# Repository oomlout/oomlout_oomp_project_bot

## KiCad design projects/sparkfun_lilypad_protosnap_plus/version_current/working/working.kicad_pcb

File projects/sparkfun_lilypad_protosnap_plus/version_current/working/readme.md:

# OOMP Project  
## LilyPad_ProtoSnap_Plus  by sparkfun  
  
oomp key: oomp_projects_flat_sparkfun_lilypad_protosnap_plus  
(snippet of original readme)  
  
SparkFun LilyPad ProtoSnap Plus  
========================================  
  
<table class="table table-hover table-striped table-bordered">  
  <tr>  
   <td><a href="https://www.sparkfun.com/products/14346"><div align="center"></div></a></center></td>  
   <td><a href="https://www.sparkfun.com/products/12922"><div align="center"></div></a></td>  
  </tr>  
  <tr>  
    <td><div align="center">LilyPad ProtoSnap Plus [<a href="https://www.sparkfun.com/products/14346">DEV-14346</a> ]</div></td>  
    <td><div align="center">LilyPad ProtoSnap Plus Kit [<a href="https://www.sparkfun.com/products/12922">DEV-12922</a>]</div></td>  
  </tr>  
</table>  
  
Snappable prototyping board with 32u4, light sensor, buzzer, button, and leds.   
  
To use the ProtoSnap Plus with Arduino, install the [SparkFun Arduino_Boards](https://github.com/sparkfun/Arduino_Boards) package for avr version 1.1.7 or later.  
  
Base examples for this board are included in the package.  Select "LilyPad USB Plus" as a board type, then see examples for that board.  
  
For extra information on Linux use, see [/Documentation/LinuxInstallation.md](https://github.com/sparkfun/LilyPad_ProtoSnap_Plus/tree/master/Documentation/LinuxInstallation.md).  
  
Repository Contents  
-------------------  
  
* **/Documentation** - pin mapping and design informatio  
  full source readme at [readme_src.md](readme_src.md)  
  
source repo at: [https://github.com/sparkfun/LilyPad_ProtoSnap_Plus](https://github.com/sparkfun/LilyPad_ProtoSnap_Plus)  
## Board  

## Schematic  

[schematic pdf](working_schematic.pdf)  
## Images

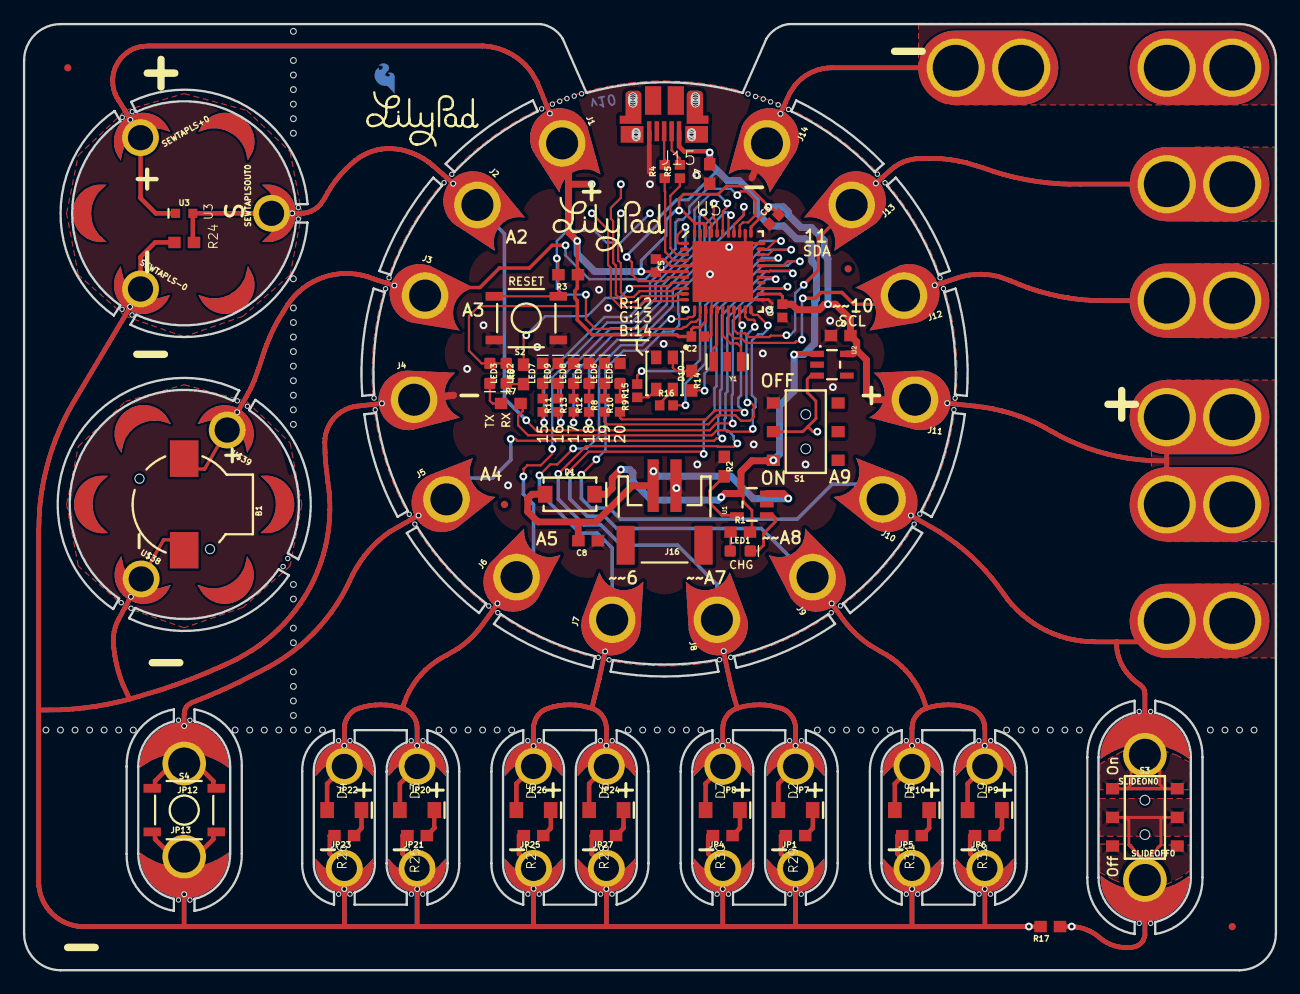
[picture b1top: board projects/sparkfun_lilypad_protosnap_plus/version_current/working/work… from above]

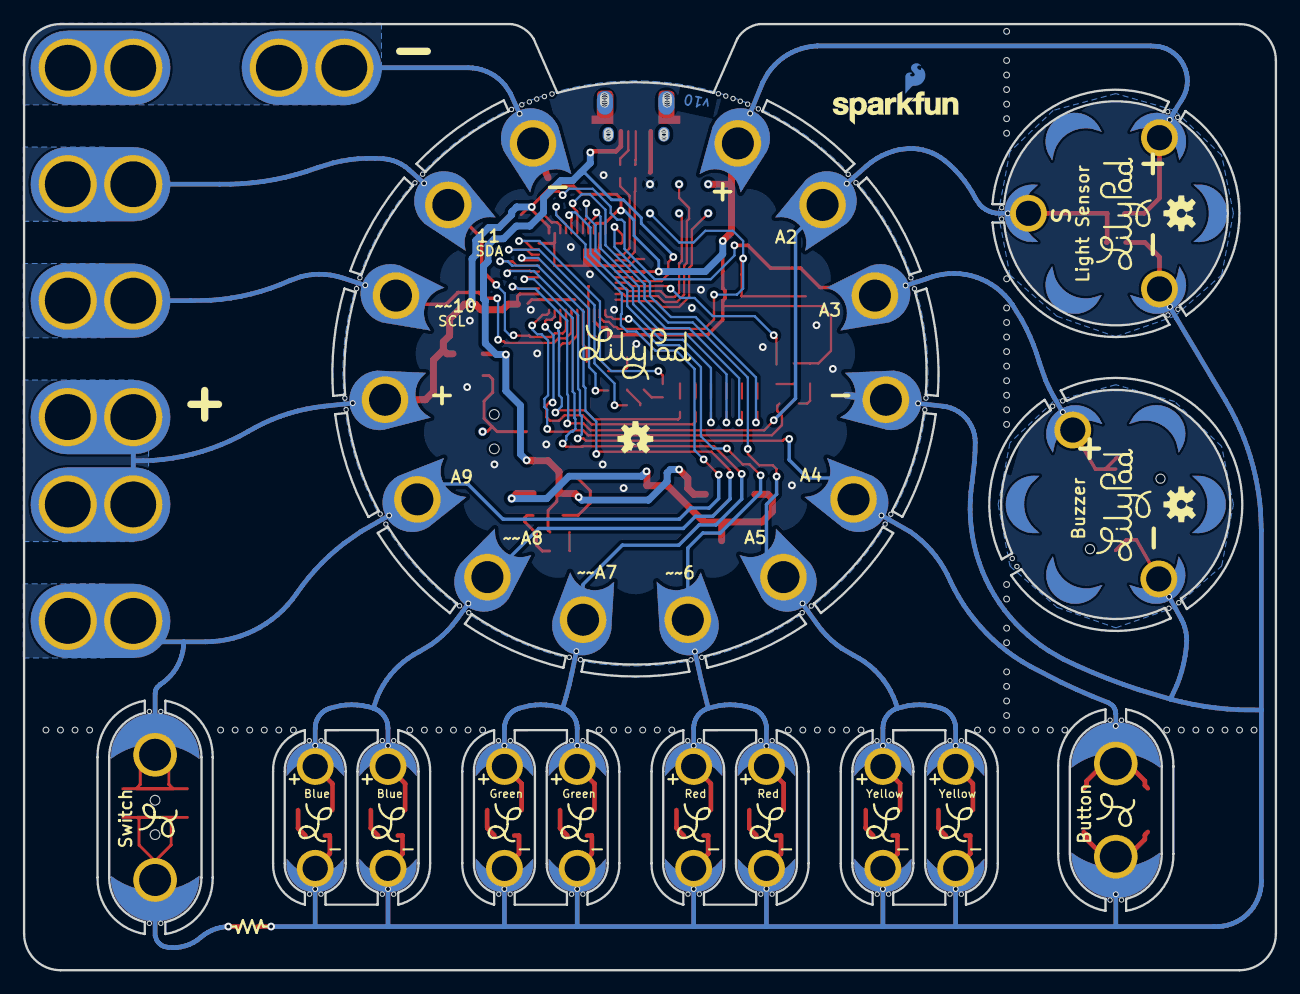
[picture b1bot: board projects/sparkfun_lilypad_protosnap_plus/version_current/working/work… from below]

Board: 2 copper layers, 109.2 x 82.6 mm, 352 parts (26 on the bottom side), 59 nets.

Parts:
@HOLE0, @HOLE1, @HOLE2, @HOLE3, @HOLE4, @HOLE5, @HOLE6, @HOLE7, @HOLE8, @HOLE9, @HOLE10, @HOLE11, @HOLE12, @HOLE13, @HOLE14, @HOLE15, @HOLE16, @HOLE17, @HOLE18, @HOLE19, @HOLE20, @HOLE21, @HOLE22, @HOLE23, @HOLE24, @HOLE25, @HOLE26, @HOLE27, @HOLE28, @HOLE29, @HOLE30, @HOLE31, @HOLE32, @HOLE33, @HOLE34, @HOLE35, @HOLE36, @HOLE37, @HOLE38, @HOLE39, @HOLE40, @HOLE41, @HOLE42, @HOLE43, @HOLE44, @HOLE45, @HOLE46, @HOLE47, @HOLE48, @HOLE49, @HOLE50, @HOLE51, @HOLE52, @HOLE53, @HOLE54, @HOLE55, @HOLE56, @HOLE57, @HOLE58, @HOLE59, @HOLE60, @HOLE61, @HOLE62, @HOLE63, @HOLE64, @HOLE65, @HOLE66, @HOLE67, @HOLE68, @HOLE69, @HOLE70, @HOLE71, @HOLE72, @HOLE73, @HOLE74, @HOLE75, @HOLE76, @HOLE77, @HOLE78, @HOLE79, @HOLE80, @HOLE81, @HOLE82, @HOLE83, @HOLE84, @HOLE85, @HOLE86, @HOLE87, @HOLE88, @HOLE89, @HOLE90, @HOLE91, @HOLE92, @HOLE93, @HOLE94, @HOLE95, @HOLE96, @HOLE97, @HOLE98, @HOLE99, @HOLE100, @HOLE101, @HOLE102, @HOLE103, @HOLE104, @HOLE105, @HOLE106, @HOLE107, @HOLE108, @HOLE109, @HOLE110, @HOLE111, @HOLE112, @HOLE113, @HOLE114, @HOLE115, @HOLE116, @HOLE117, @HOLE118, @HOLE119, @HOLE120, @HOLE121, @HOLE122, @HOLE123, @HOLE124, @HOLE125, @HOLE126, @HOLE127, @HOLE128, @HOLE129, @HOLE130, @HOLE131, @HOLE132, @HOLE133, @HOLE134, @HOLE135, @HOLE136, @HOLE137, @HOLE138, @HOLE139, @HOLE140, @HOLE141, @HOLE142, @HOLE143, @HOLE144, @HOLE145, @HOLE146, @HOLE147, @HOLE148, @HOLE149, @HOLE150, @HOLE151, @HOLE152, @HOLE153, @HOLE154: (no value)
B1: Buzzer; BUZZER-CCV
C2, C3, C4: 0.1uF; 0402
C5: 1.0uF; 0402
C6, C7, C8: 4.7uF; 0603
D1: 3A/40V/500mV; SMA-DIODE
D2, D7: GREEN; LED-1206
D3, D4: Yellow; LED-1206
D5, D6: RED; LED-1206
D8, D9: BLUE; LED-1206
D10: XZM2CRKM2DGFBB45SCCB; PLCC4SMDLED
FRAME1: FRAME-LETTER; CREATIVE_COMMONS
FRAME2: FRAME-LETTERNO_PACKAGE; DUMMY
J1, J2, J3, J4, J5, J6, J7, J8, J9, J10, J11, J12, J13, J14: SEWTAP_LONG-2SIDE; PETAL-LONG-1-2SIDE
J15: AMP FCI 10103594-0001LF; USB-MICROB-PTH
J16: JST-2-SMD
JP1, JP4, JP5, JP6, JP7, JP8, JP9, JP10, JP20, JP21, JP22, JP23, JP24, JP25, JP26, JP27: SEWTAP_SMALL-2SIDE; PETAL-SMALL-2SIDE
JP2, JP3, JP11, JP14: FIDUCIALUFIDUCIAL; MICRO-FIDUCIAL
JP12, JP13: SEWTAP_MEDIUM-2SIDE; PETAL-MEDIUM-2SIDE
L001, L002, L003, L004: LOGO-L
LED1: RED; LED-0603
LED2: Yellow; LED-0603
LED3: GREEN; LED-0603
LED4, LED5, LED6, LED7, LED8, LED9: WHITE; LED-0603
LOGO1: SFE_LOGO_NAME.1_INCH; SFE_LOGO_NAME_.1
LOGO2: SFE_LOGO_FLAME.1EXP; SFE_LOGO_FLAME_COPPER_EXPOSED_.1
LOGO4, LOGO5, LOGO6: OSHW-LOGOS; OSHW-LOGO-S
R1, R7, R14: 330; 0603
R2, R3, R24: 10k; 0603
R4, R5, R15, R16: 22; 0402
R6: 2.2k; 0603
R8, R9, R10, R11, R12, R13: 470; 0402
R17: 1k; 0603
R25, R26, R29, R30: 100; 0603
R27, R28, R31, R32: 150; 0603
S1, S3: SWITCH_DPDT_SMD_AYZ0202
S2: !RESET; TACTILE_SWITCH_SMD_5.2MM
S4: MOMENTARY-SWITCH-SPST-SMD-5.2-REDUNDANT; TACTILE_SWITCH_SMD_5.2MM
SEWTAPLS+0: PLUS; PETAL-SMALL-2SIDE
SEWTAPLS-0: MINUS; PETAL-SMALL-2SIDE
SEWTAPLSOUT0: OUT; PETAL-SMALL-2SIDE
SLIDEOFF0: SEWTAP_MEDIUM-2SIDE; PETAL-MEDIUM-2SIDE
SLIDEON0: SEWTAP_MEDIUM-2SIDE; PETAL-MEDIUM-2SIDE
ST1, ST2, ST3: SEWTAP-NOHOLE_SM_NH; PETAL-SMALL-NOHOLE
TP1, TP2, TP3, TP4, TP5, TP6, TP7, TP8: TEST-POINT3; PAD.03X.03
U1: MCP73831; SOT23-5
U2: 3.3V; SOT23-5
U3: ALS-PT19
U5: 32U4; QFN-44-PAD_1_1-LESS_PASTE
U$1, U$5, U$6, U$13, U$43: LILYLOGO_SHORT; LILYPAD-WEARABLES_LOGO-LILYPAD
U$3, U$9, U$11, U$15, U$17, U$19, U$21, U$23, U$25, U$27, U$29, U$31, U$33, U$34: PETAL_PAD_OFF
U$7, U$8, U$10, U$12, U$16, U$18, U$20, U$22, U$24, U$26, U$28, U$30, U$32: PETAL_SPACE_OFF
U$35, U$36, U$37, U$40: SEWTAP-NOHOLE_SM_NH; PETAL-SMALL-NOHOLE
U$38, U$39: SEWTAP_SMALL-2SIDE; PETAL-SMALL-2SIDE
U$41, U$42, U$51/SDA0, U$52/SCL0, U$52/SCL1, U$53, U$54: GATOR_HOLE_PAIR; GATOR_HOLES
U$44: SPECIAL_INSTRUCTIONS-ORDERING; ORDERING_INSTRUCTIONS
U$45, U$46, U$48, U$49, U$50: LOGO-L
U$51, U$52, U$55, U$56, U$57, U$58, U$59, U$60, U$61, U$62, U$63, U$64, U$65, U$66, U$67, U$68, U$70, U$71: ROUTE_TICKS
U$73: LILYLOGO_ABR; LILYPAD-WEARABLES_LOGO-L
Y1: 8MHz; RESONATOR-SMD

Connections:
3.3V: C2.2, C3.2, C4.2, C5.2, C6.2, J1.1, J11.1, LED2.A, LED3.A, R3.1, SEWTAPLS+0.1, TP6.P$1, U2.5, U3.C, U5.6, U5.14, U5.24, U5.34, U5.42, U5.44, U$41.P$1, U$41.P$2, U$42.P$1, U$42.P$2
BG_LED0: R8.2, U5.38
BG_LED1: R9.2, U5.20
BG_LED2: R10.2, U5.21
BG_LED3: R11.2, U5.1
BG_LED4: R12.2, U5.40
BG_LED5: R13.2, U5.41
D2: J2.1, R24.2, SEWTAPLSOUT0.1, U3.E, U5.25
D3: B1.+, J3.1, U5.36, U$39.1
D4: J5.1, JP12.1, S4.1, S4.2, U5.28
D5: D3.A, D4.A, J6.1, JP20.1, JP22.1, U5.39
D6: D5.A, D6.A, J7.1, JP24.1, JP26.1, U5.12
D7: D2.A, D7.A, J8.1, JP7.1, JP8.1, U5.27
D8: D8.A, D9.A, J9.1, JP9.1, JP10.1, U5.29
D9: J10.1, S3.1, S3.4, SLIDEON0.1, U5.37, U$52/SCL1.P$1, U$52/SCL1.P$2
D10: J12.1, U5.18, U$52/SCL0.P$1, U$52/SCL0.P$2
D11: J13.1, U5.19, U$51/SDA0.P$1, U$51/SDA0.P$2
D+: R4.1, U5.4
D-: R5.1, U5.3
GND: B1.-, C2.1, C3.1, C4.1, C5.1, C6.1, C7.1, C8.1, D10.4, J4.1, J14.1, J15.GND, J16.1, JP1.1, JP4.1, JP5.1, JP6.1, JP13.1, JP21.1, JP23.1, JP25.1, JP27.1, LED4.C, LED5.C, LED6.C, LED7.C, LED8.C, LED9.C, R2.1, R17.2, R24.1, R25.1, R26.1, R27.1, R28.1, R29.1, R30.1, R31.1, R32.1, S1.3, S2.1, S2.2, S4.3, S4.4, SEWTAPLS-0.1, TP5.P$1, U1.2, U2.2, U5.5, U5.15, U5.23, U5.33, U5.35, U5.43, U$38.1, U$53.P$1, U$53.P$2, U$54.P$1, U$54.P$2, Y1.2
MISO: TP1.P$1, U5.11
MOSI: TP2.P$1, U5.10
unnamed: LED2.C, R6.1
unnamed: S1.2, TP8.P$1, U2.3
unnamed: LED1.A, R1.1
unnamed: LED1.C, U1.1
unnamed: U5.17, Y1.1
unnamed: R2.2, U1.5
unnamed: U5.16, Y1.3
unnamed: D10.2, R16.1
unnamed: LED7.A, R11.1
unnamed: LED6.A, R10.1
unnamed: LED5.A, R9.1
unnamed: LED8.A, R12.1
unnamed: LED9.A, R13.1
unnamed: D10.3, R15.1
unnamed: D10.1, R14.1
unnamed: LED4.A, R8.1
unnamed: J15.D-, R5.2
unnamed: J15.D+, R4.2
unnamed: LED3.C, R7.1
unnamed: D3.C, R25.2
unnamed: D4.C, R26.2
unnamed: D5.C, R27.2
unnamed: D6.C, R28.2
unnamed: D2.C, R29.2
RESET: R3.2, S2.3, S2.4, TP4.P$1, U5.13
RGB_B: R15.2, U5.32
RGB_G: R16.2, U5.31
RGB_R: R14.2, U5.30
RX_LED: R6.2, U5.8
SCK: TP3.P$1, U5.9
SEWTAP+1: D7.C, R30.2
TX_LED: R7.2, U5.22
VCC_1: C7.2, D1.C, J15.VBUS, R1.2, S1.1, U1.4, U2.1, U5.7
V_BATT: C8.2, D1.A, J16.2, TP7.P$1, U1.3
X003: D8.C, R31.2
X004: D9.C, R32.2
X005: R17.1, S3.2, S3.5, SLIDEOFF0.1

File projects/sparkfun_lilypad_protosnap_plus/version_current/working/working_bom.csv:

"Id";"Designator";"Footprint";"Quantity";"Designation";"Supplier and ref";
1;"@HOLE147,@HOLE118,@HOLE117,@HOLE103,@HOLE99,@HOLE35,@HOLE28,@HOLE144,@HOLE55,@HOLE115,@HOLE102,@HOLE146,@HOLE45,@HOLE151,@HOLE29,@HOLE77,@HOLE61,@HOLE40,@HOLE1,@HOLE81,@HOLE137,@HOLE21,@HOLE2,@HOLE25,@HOLE47,@HOLE18,@HOLE149,@HOLE5,@HOLE93,@HOLE132,@HOLE44,@HOLE13,@HOLE59,@HOLE57,@HOLE133,@HOLE120,@HOLE134,@HOLE87,@HOLE136,@HOLE107,@HOLE73,@HOLE68,@HOLE121,@HOLE76,@HOLE70,@HOLE30,@HOLE52,@HOLE31,@HOLE19,@HOLE50,@HOLE69,@HOLE71,@HOLE20,@HOLE104,@HOLE91,@HOLE79,@HOLE105,@HOLE72,@HOLE111,@HOLE83,@HOLE123,@HOLE67,@HOLE56,@HOLE9,@HOLE153,@HOLE108,@HOLE80,@HOLE129,@HOLE48,@HOLE125,@HOLE89,@HOLE126,@HOLE98,@HOLE90,@HOLE36,@HOLE66,@HOLE63,@HOLE0,@HOLE7,@HOLE114,@HOLE143,@HOLE8,@HOLE97,@HOLE11,@HOLE142,@HOLE14,@HOLE152,@HOLE122,@HOLE74,@HOLE116,@HOLE46,@HOLE110,@HOLE131,@HOLE22,@HOLE27,@HOLE85,@HOLE51,@HOLE145,@HOLE32,@HOLE54,@HOLE4,@HOLE140,@HOLE113,@HOLE78,@HOLE10,@HOLE6,@HOLE39,@HOLE43,@HOLE135,@HOLE96,@HOLE15,@HOLE41,@HOLE17,@HOLE34,@HOLE84,@HOLE94,@HOLE100,@HOLE124,@HOLE86,@HOLE58,@HOLE75,@HOLE106,@HOLE128,@HOLE141,@HOLE92,@HOLE53,@HOLE130,@HOLE42,@HOLE33,@HOLE65,@HOLE64,@HOLE16,@HOLE38,@HOLE119,@HOLE95,@HOLE88,@HOLE24,@HOLE82,@HOLE101,@HOLE62,@HOLE109,@HOLE138,@HOLE49,@HOLE37,@HOLE3,@HOLE139,@HOLE112,@HOLE23,@HOLE150,@HOLE154,@HOLE127,@HOLE60,@HOLE148,@HOLE12,@HOLE26";"";155;"";;;
2;"U$52/SCL0,U$52/SCL1,U$51/SDA0,U$42,U$41,U$54,U$53";"GATOR_HOLES";7;"GATOR_HOLE_PAIR";;;
3;"LED4,LED6,LED8,LED9,LED5,LED7";"LED-0603";6;"WHITE";;;
4;"U$58,U$71,U$66,U$68,U$52,U$63,U$60,U$57,U$65,U$67,U$61,U$64,U$62,U$56,U$51,U$70,U$59,U$55";"ROUTE_TICKS";18;"";;;
5;"JP23,JP24,JP25,JP26,JP5,JP21,JP22,JP10,U$39,JP7,JP8,JP20,JP6,JP9,JP27,JP1,U$38,JP4";"PETAL-SMALL-2SIDE";18;"SEWTAP_SMALL-2SIDE";;;
6;"R16,R5,R4,R15";"0402";4;"22";;;
7;"D9,D8";"LED-1206";2;"BLUE";;;
8;"J2,J5,J1,J4,J6,J3,J7,J11,J9,J13,J8,J14,J10,J12";"PETAL-LONG-1-2SIDE";14;"SEWTAP_LONG-2SIDE";;;
9;"R11,R8,R9,R10,R13,R12";"0402";6;"470";;;
10;"U$32,U$28,U$20,U$24,U$16,U$7,U$18,U$8,U$30,U$26,U$22,U$10,U$12";"PETAL_SPACE_OFF";13;"";;;
11;"R24,R2,R3";"0603";3;"10k";;;
12;"Y1";"RESONATOR-SMD";1;"8MHz";;;
13;"S4";"TACTILE_SWITCH_SMD_5.2MM";1;"MOMENTARY-SWITCH-SPST-SMD-5.2-REDUNDANT";;;
14;"ST3,U$36,U$35,U$40,U$37,ST1,ST2";"PETAL-SMALL-NOHOLE";7;"SEWTAP-NOHOLE_SM_NH";;;
15;"R26,R25,R29,R30";"0603";4;"100";;;
16;"R6";"0603";1;"2.2k";;;
17;"U$27,U$31,U$21,U$25,U$11,U$15,U$3,U$33,U$19,U$9,U$29,U$23,U$34,U$17";"PETAL_PAD_OFF";14;"";;;
18;"C5";"0402";1;"1.0uF";;;
19;"S3,S1";"SWITCH_DPDT_SMD_AYZ0202";2;"";;;
20;"FRAME2";"DUMMY";1;"FRAME-LETTERNO_PACKAGE";;;
21;"C8,C7,C6";"0603";3;"4.7uF";;;
22;"J16";"JST-2-SMD";1;"";;;
23;"JP12,SLIDEOFF0,SLIDEON0,JP13";"PETAL-MEDIUM-2SIDE";4;"SEWTAP_MEDIUM-2SIDE";;;
24;"D10";"PLCC4SMDLED";1;"XZM2CRKM2DGFBB45SCCB";;;
25;"R32,R31,R27,R28";"0603";4;"150";;;
26;"S2";"TACTILE_SWITCH_SMD_5.2MM";1;"!RESET";;;
27;"LED1";"LED-0603";1;"RED";;;
28;"LED3";"LED-0603";1;"GREEN";;;
29;"R17";"0603";1;"1k";;;
30;"U$43,U$13,U$6,U$5,U$1";"LILYPAD-WEARABLES_LOGO-LILYPAD";5;"LILYLOGO_SHORT";;;
31;"D4,D3";"LED-1206";2;"Yellow";;;
32;"JP3,JP11,JP2,JP14";"MICRO-FIDUCIAL";4;"FIDUCIALUFIDUCIAL";;;
33;"U2";"SOT23-5";1;"3.3V";;;
34;"D6,D5";"LED-1206";2;"RED";;;
35;"U$44";"ORDERING_INSTRUCTIONS";1;"SPECIAL_INSTRUCTIONS-ORDERING";;;
36;"R7,R14,R1";"0603";3;"330";;;
37;"U3";"ALS-PT19";1;"ALS-PT19";;;
38;"C2,C3,C4";"0402";3;"0.1uF";;;
39;"LED2";"LED-0603";1;"Yellow";;;
40;"D2,D7";"LED-1206";2;"GREEN";;;
41;"U1";"SOT23-5";1;"MCP73831";;;
42;"U5";"QFN-44-PAD_1_1-LESS_PASTE";1;"32U4";;;
43;"D1";"SMA-DIODE";1;"3A/40V/500mV";;;
44;"FRAME1";"CREATIVE_COMMONS";1;"FRAME-LETTER";;;
45;"J15";"USB-MICROB-PTH";1;"AMP FCI 10103594-0001LF";;;
46;"B1";"BUZZER-CCV";1;"Buzzer";;;
47;"SEWTAPLSOUT0";"PETAL-SMALL-2SIDE";1;"OUT";;;
48;"SEWTAPLS-0";"PETAL-SMALL-2SIDE";1;"MINUS";;;
49;"SEWTAPLS+0";"PETAL-SMALL-2SIDE";1;"PLUS";;;
50;"U$49,L001,U$45,U$48,L004,L002,U$46,L003,U$50";"LOGO-L";9;"";;;
51;"TP6,TP2,TP7,TP1,TP8,TP3,TP4,TP5";"PAD.03X.03";8;"TEST-POINT3";;;
52;"U$73";"LILYPAD-WEARABLES_LOGO-L";1;"LILYLOGO_ABR";;;
53;"LOGO6,LOGO5,LOGO4";"OSHW-LOGO-S";3;"OSHW-LOGOS";;;
54;"LOGO1";"SFE_LOGO_NAME_.1";1;"SFE_LOGO_NAME.1_INCH";;;
55;"LOGO2";"SFE_LOGO_FLAME_COPPER_EXPOSED_.1";1;"SFE_LOGO_FLAME.1EXP";;;

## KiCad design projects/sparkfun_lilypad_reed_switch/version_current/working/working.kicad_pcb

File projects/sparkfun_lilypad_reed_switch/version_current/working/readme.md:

# OOMP Project  
## LilyPad_Reed_Switch  by sparkfun  
  
oomp key: oomp_projects_flat_sparkfun_lilypad_reed_switch  
(snippet of original readme)  
  
SparkFun LilyPad Reed Switch  
========================================  

[*LilyPad Reed Switch (DEV-13343)*](https://www.sparkfun.com/products/13343)  
  
A magnetically-activated switch designed for easy use in e-textiles projects.  
  
Repository Contents  
-------------------  
  
* **/Hardware** - Eagle design files (.brd, .sch)  
* **/Production** - Production panel files (.brd)  
  
Documentation  
--------------  
  
* **[Hookup Guide](https://learn.sparkfun.com/tutorials/lilypad-reed-switch-hookup-guide?_ga=1.257312139.1628578815.1436805952)** - Basic hookup guide for the LilyPad Reed Switch.  
* **[SparkFun Fritzing repo](https://github.com/sparkfun/Fritzing_Parts)** - Fritzing diagrams for SparkFun products.  
* **[SparkFun 3D Model repo](https://github.com/sparkfun/3D_Models)** - 3D models of SparkFun products.   

License Information  
-------------------  
  
This product is _**open source**_!   
  
Please review the LICENSE.md file for license information.   
  
If you have any questions or concerns on licensing, please contact techsupport@sparkfun.com.  
  
Distributed as-is; no warranty is given.  
  
<3 <3 <3 Your friends at SparkFun.  
  
_Created in collaboration with Dr. Leah Buechley_  
  
  full source readme at [readme_src.md](readme_src.md)  
  
source repo at: [https://github.com/sparkfun/LilyPad_Reed_Switch](https://github.com/sparkfun/LilyPad_Reed_Switch)  
## Board  

## Schematic  

[schematic pdf](working_schematic.pdf)  
## Images

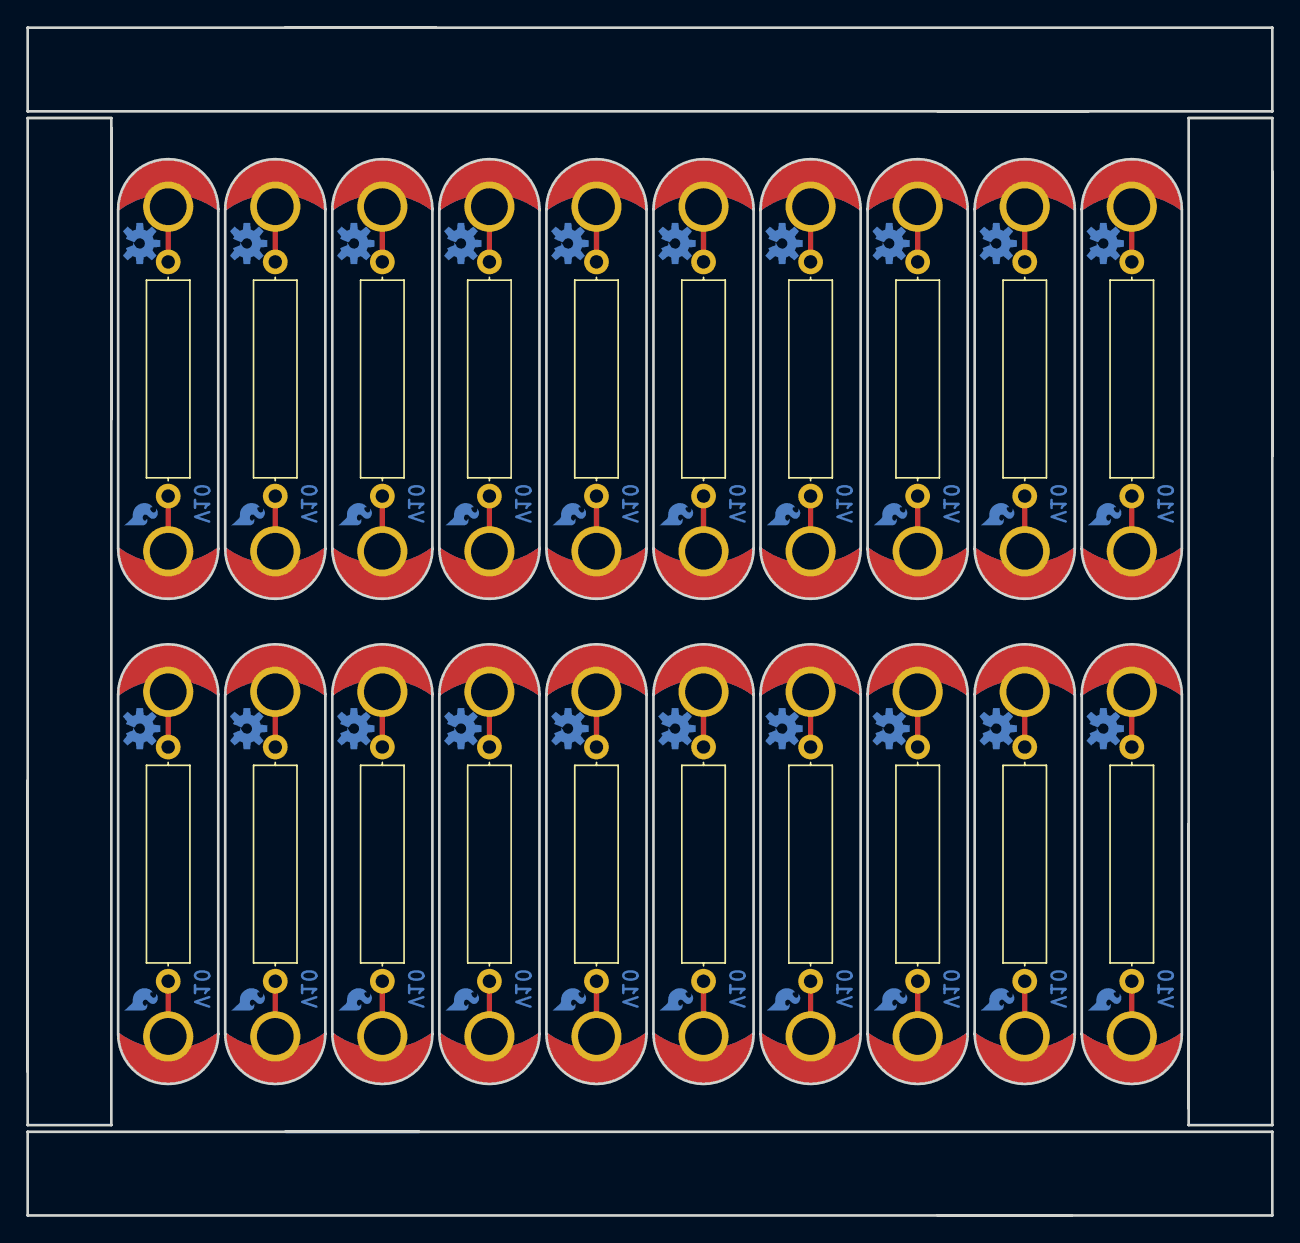
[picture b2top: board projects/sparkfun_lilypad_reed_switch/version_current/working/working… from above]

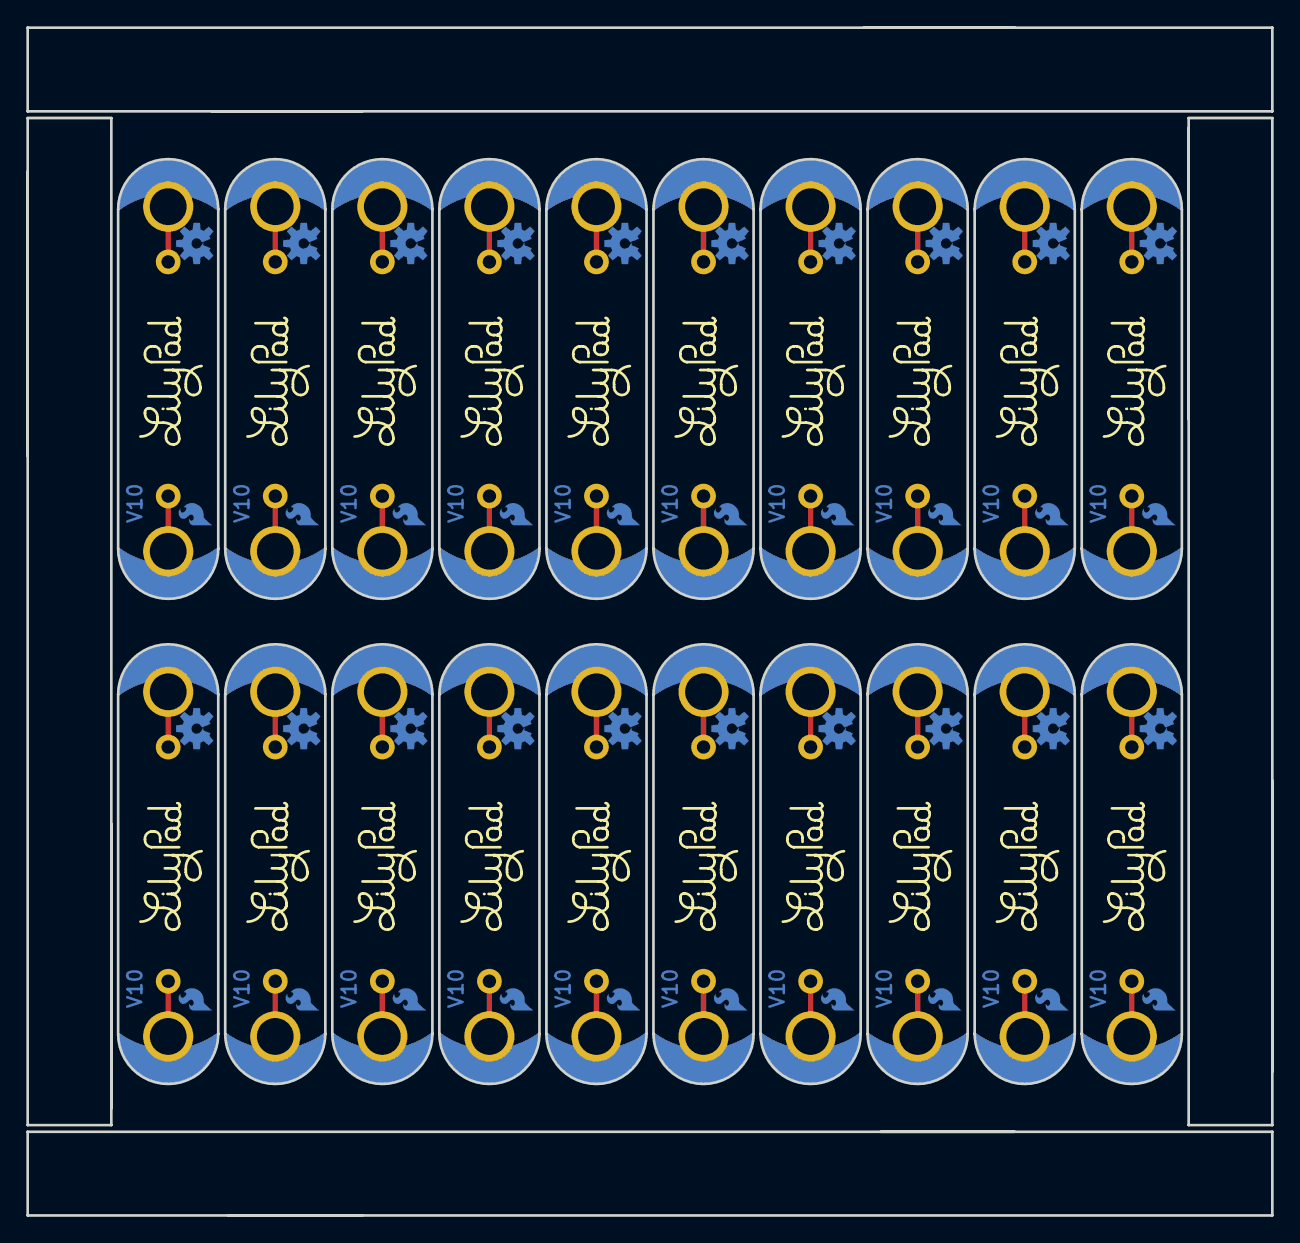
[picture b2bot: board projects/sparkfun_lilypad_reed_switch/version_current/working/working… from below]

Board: 4 copper layers, 94.5 x 90.2 mm, 120 parts (60 on the bottom side), 40 nets.

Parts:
LOGO1, LOGO3, LOGO5, LOGO7, LOGO9, LOGO11, LOGO13, LOGO15, LOGO17, LOGO19, LOGO21, LOGO23, LOGO25, LOGO27, LOGO29, LOGO31, LOGO33, LOGO35, LOGO37, LOGO39: OSHW-LOGOS-COPPER; OSHW-LOGO-S_COPPER
LOGO2, LOGO4, LOGO6, LOGO8, LOGO10, LOGO12, LOGO14, LOGO16, LOGO18, LOGO20, LOGO22, LOGO24, LOGO26, LOGO28, LOGO30, LOGO32, LOGO34, LOGO36, LOGO38, LOGO40: SFE_LOGO_FLAME.1COP; SFE_LOGO_FLAME_COPPER_.1
S1, S2, S3, S4, S5, S6, S7, S8, S9, S10, S11, S12, S13, S14, S15, S16, S17, S18, S19, S20: REED; REED_SWITCH_PLASTIC
SLIDEOFF0, SLIDEOFF1, SLIDEOFF2, SLIDEOFF3, SLIDEOFF4, SLIDEOFF5, SLIDEOFF6, SLIDEOFF7, SLIDEOFF8, SLIDEOFF9, SLIDEOFF10, SLIDEOFF11, SLIDEOFF12, SLIDEOFF13, SLIDEOFF14, SLIDEOFF15, SLIDEOFF16, SLIDEOFF17, SLIDEOFF18, SLIDEOFF19: SEWTAP8; PETAL-MEDIUM-2SIDE
SLIDEON0, SLIDEON1, SLIDEON2, SLIDEON3, SLIDEON4, SLIDEON5, SLIDEON6, SLIDEON7, SLIDEON8, SLIDEON9, SLIDEON10, SLIDEON11, SLIDEON12, SLIDEON13, SLIDEON14, SLIDEON15, SLIDEON16, SLIDEON17, SLIDEON18, SLIDEON19: SEWTAP8; PETAL-MEDIUM-2SIDE
U$1, U$2, U$3, U$4, U$5, U$6, U$7, U$8, U$9, U$10, U$11, U$12, U$13, U$14, U$15, U$16, U$17, U$18, U$19, U$20: LOGO-LPLP; LOGO-LILYPAD

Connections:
unnamed: S1.P$2, SLIDEOFF0.1
unnamed: S1.P$1, SLIDEON0.1
unnamed: S2.P$2, SLIDEOFF1.1
unnamed: S2.P$1, SLIDEON1.1
unnamed: S3.P$2, SLIDEOFF2.1
unnamed: S3.P$1, SLIDEON2.1
unnamed: S4.P$2, SLIDEOFF3.1
unnamed: S4.P$1, SLIDEON3.1
unnamed: S5.P$2, SLIDEOFF4.1
unnamed: S5.P$1, SLIDEON4.1
unnamed: S6.P$2, SLIDEOFF5.1
unnamed: S6.P$1, SLIDEON5.1
unnamed: S7.P$2, SLIDEOFF6.1
unnamed: S7.P$1, SLIDEON6.1
unnamed: S8.P$2, SLIDEOFF7.1
unnamed: S8.P$1, SLIDEON7.1
unnamed: S9.P$2, SLIDEOFF8.1
unnamed: S9.P$1, SLIDEON8.1
unnamed: S10.P$2, SLIDEOFF9.1
unnamed: S10.P$1, SLIDEON9.1
unnamed: S11.P$2, SLIDEOFF10.1
unnamed: S11.P$1, SLIDEON10.1
unnamed: S12.P$2, SLIDEOFF11.1
unnamed: S12.P$1, SLIDEON11.1
unnamed: S13.P$2, SLIDEOFF12.1
unnamed: S13.P$1, SLIDEON12.1
unnamed: S14.P$2, SLIDEOFF13.1
unnamed: S14.P$1, SLIDEON13.1
unnamed: S15.P$2, SLIDEOFF14.1
unnamed: S15.P$1, SLIDEON14.1
unnamed: S16.P$2, SLIDEOFF15.1
unnamed: S16.P$1, SLIDEON15.1
unnamed: S17.P$2, SLIDEOFF16.1
unnamed: S17.P$1, SLIDEON16.1
unnamed: S18.P$2, SLIDEOFF17.1
unnamed: S18.P$1, SLIDEON17.1
unnamed: S19.P$2, SLIDEOFF18.1
unnamed: S19.P$1, SLIDEON18.1
unnamed: S20.P$2, SLIDEOFF19.1
unnamed: S20.P$1, SLIDEON19.1

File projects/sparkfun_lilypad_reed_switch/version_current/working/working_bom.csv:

Row,Description,Part,References,Value,Footprint,Quantity Per PCB,Status,Datasheet
1,,FRAME-LETTER,FRAME1,FRAME-LETTER,CREATIVE_COMMONS,1, ,
2,,OSHW-LOGOS-COPPER,LOGO1,OSHW-LOGOS-COPPER,OSHW-LOGO-S_COPPER,1, ,
3,,SFE_LOGO_FLAME.1COP,LOGO2,SFE_LOGO_FLAME.1COP,SFE_LOGO_FLAME_COPPER_.1,1, ,
4,,SWITCH-MOMENTARY-2PTH_REED2,S1,SWITCH-MOMENTARY-2PTH_REED2,REED_SWITCH_PLASTIC,1, ,
5,,SEWTAP8,SLIDEOFF0 SLIDEON0,SEWTAP8,PETAL-MEDIUM-2SIDE,2, ,
6,,LOGO-LPLP,U$1,LOGO-LPLP,LOGO-LILYPAD,1, ,





Project info:
Schematic:,working
Variant:,default
Revision:,
Date:,2023-08-06_12-56-04
KiCad Version:,7.0.6-7.0.6~ubuntu22.04.1
Statistics:
Component Groups:,6
Component Count:,7 (0 SMD/ 0 THT)
Fitted Components:,7 (0 SMD/ 0 THT)
Number of PCBs:,1
Total Components:,7

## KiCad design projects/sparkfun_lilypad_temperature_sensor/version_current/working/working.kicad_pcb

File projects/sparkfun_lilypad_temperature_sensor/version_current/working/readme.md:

# OOMP Project  
## LilyPad_Temperature_Sensor  by sparkfun  
  
oomp key: oomp_projects_flat_sparkfun_lilypad_temperature_sensor  
(snippet of original readme)  
  
LilyPad Temperature Sensor  
========================================  

[*LilyPad Temperature Sensor (DEV-08777)*](https://www.sparkfun.com/products/8777)  
  
Detecting temperature changes has never been easier.   
The MCP9700 is a small thermistor type temperature sensor.   
This sensor will output 0.5V at 0 degrees C, 0.75V at 25 C, and 10mV per degree C. Doing an analog to digital conversion on the signal line will allow you to establish the local ambient temperature.   
Detect physical touch based on body heat and ambient conditions with this small sensor.  
  
Repository Contents  
-------------------  
* **/Firmware** - Arduino Example code   
* **/Hardware** - Eagle design files (.brd, .sch)  
* **/Production** - Production panel files (.brd)  
  
Documentation  
--------------  
* **[Hookup Guide](https://learn.sparkfun.com/tutorials/lilypad-temperature-sensor-hookup-guide)** - Basic Hookup Guide for the LilyPad temperature sensor.  
* **[SparkFun Fritzing repo](https://github.com/sparkfun/Fritzing_Parts)** - Fritzing diagrams for SparkFun products.  
* **[SparkFun 3D Model repo](https://github.com/sparkfun/3D_Models)** - 3D models of SparkFun products.   
  
License Information  
-------------------  
This product is _**open source**_!   
  
The **hardware** is released under [Creative Commons ShareAlike 4.0 International](https://creativecommons.org/licenses/by-sa/4.0/).  
  
Please use, reuse, and modify these files as you se  
  full source readme at [readme_src.md](readme_src.md)  
  
source repo at: [https://github.com/sparkfun/LilyPad_Temperature_Sensor](https://github.com/sparkfun/LilyPad_Temperature_Sensor)  
## Board  

## Schematic  

[schematic pdf](working_schematic.pdf)  
## Images

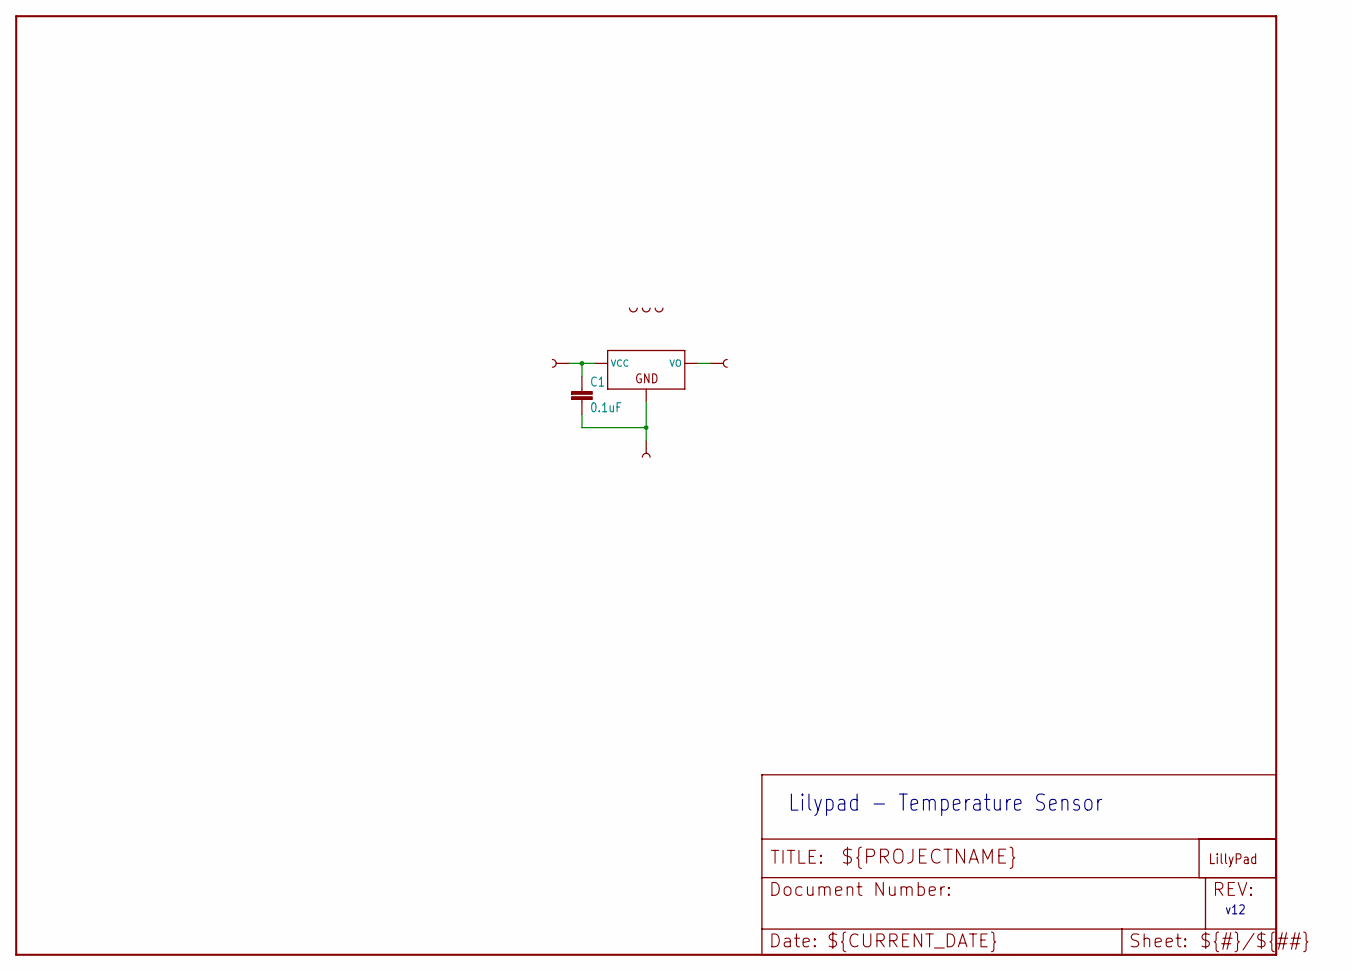
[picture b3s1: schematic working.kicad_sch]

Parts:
C1: 0.1uF; 0603-CAP
TEMP1, TEMP2, TEMP3: SEWTAP-NOHOLE2; PETAL-NOHOLE-2SIDE
TEMP+0: SEWTAP6; PETAL-SMALL-2SIDE
TEMP-0: SEWTAP6; PETAL-SMALL-2SIDE
TEMPS0: SEWTAP6; PETAL-SMALL-2SIDE
U1: MCP9700SMD; SOT23-3
U$2: LOGO-LPLP; LOGO-LILYPAD

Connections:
GND: C1.2, TEMP-0.1, U1.3 (GND)
VCC: C1.1, TEMP+0.1, U1.1 (VCC)
VO: TEMPS0.1, U1.2 (VO)

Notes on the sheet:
v12
Lilypad - Temperature Sensor

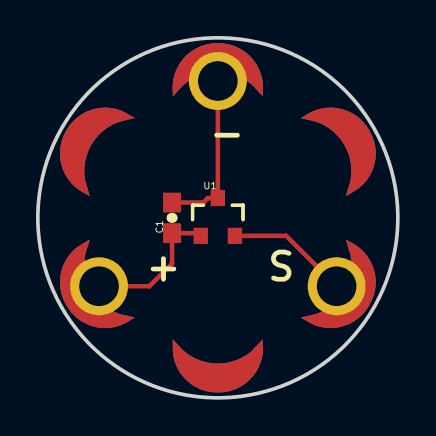
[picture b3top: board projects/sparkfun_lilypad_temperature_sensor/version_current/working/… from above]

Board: 2 copper layers, 20.0 x 20.0 mm, 9 parts (1 on the bottom side), 3 nets.

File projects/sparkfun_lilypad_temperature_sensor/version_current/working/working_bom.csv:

"Id";"Designator";"Footprint";"Quantity";"Designation";"Supplier and ref";
1;"TEMP+0,TEMPS0,TEMP-0";"PETAL-SMALL-2SIDE";3;"SEWTAP6";;;
2;"TEMP3,TEMP1,TEMP2";"PETAL-NOHOLE-2SIDE";3;"SEWTAP-NOHOLE2";;;
3;"U1";"SOT23-3";1;"MCP9700";;;
4;"C1";"0603-CAP";1;"0.1uF";;;
5;"U$2";"LOGO-LILYPAD";1;"LOGO-LPLP";;;

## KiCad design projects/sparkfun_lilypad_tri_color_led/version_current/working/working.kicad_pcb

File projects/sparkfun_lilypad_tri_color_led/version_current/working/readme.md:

# LilyPad_Tri-Color_LED by sparkfun  
This is a harvested standardized copy of a project from github.  
The original project can be found at:  
https://github.com/sparkfun/LilyPad_Tri-Color_LED  
Please consult that link for additional, details, files, and license information.  
Note: It was auto harvested and if the original repo had more than one board file or anything out of the ordinary the files here are likely not representative.

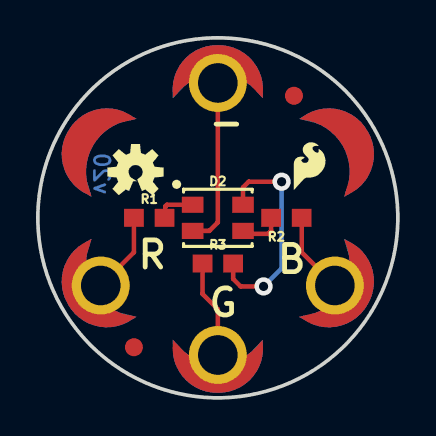
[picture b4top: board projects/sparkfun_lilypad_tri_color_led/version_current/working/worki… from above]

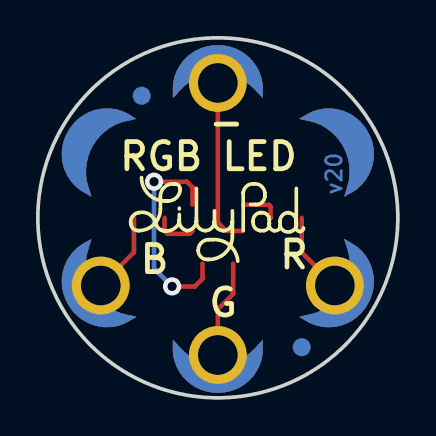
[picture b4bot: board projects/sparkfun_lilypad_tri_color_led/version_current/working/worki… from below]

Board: 2 copper layers, 20.0 x 20.0 mm, 20 parts (3 on the bottom side), 7 nets.

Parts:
D2: XZM2CRKM2DGFBB45SCCB; PLCC4SMDLED
FD1, FD2, FD3, FD4: FIDUCIAL1X2; FIDUCIAL-1X2
FRAME1: FRAME-LETTER; CREATIVE_COMMONS
LOGO1: REVISION
LOGO2: OSHW-LOGOS; OSHW-LOGO-S
LOGO3: SFE_LOGO_FLAME.1_INCH; SFE_LOGO_FLAME_.1
R1: 200; 0603
R2, R3: 100; 0603
U$1: LOGO-LPLP; LOGO-LILYPAD
U$2, U$3: SEWTAP-NOHOLE2; PETAL-NOHOLE-2SIDE
U$4: ORDERING_INSTRUCTIONS
U$7, U$8, U$9, U$10: SEWTAP6; PETAL-SMALL-2SIDE

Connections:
B: R2.1, U$9.1
BLU: D2.3, R2.2
G: R3.1, U$8.1
GND: D2.4, U$10.1
GRN: D2.2, R3.2
R: R1.1, U$7.1
RED: D2.1, R1.2

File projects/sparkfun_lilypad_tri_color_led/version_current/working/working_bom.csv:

Row,Description,Part,References,Value,Footprint,Quantity Per PCB,Status,Datasheet
1,,SUNLEDSMD1,D2,SUNLEDSMD1,PLCC4SMDLED,1, ,
2,,FRAME-LETTER,FRAME1,FRAME-LETTER,CREATIVE_COMMONS,1, ,
3,,OSHW-LOGOS,LOGO2,OSHW-LOGOS,OSHW-LOGO-S,1, ,
4,,REVISION,LOGO1,REVISION,REVISION,1, ,
5,,SFE_LOGO_FLAME.1_INCH,LOGO3,SFE_LOGO_FLAME.1_INCH,SFE_LOGO_FLAME_.1,1, ,
6,,100OHM-0603-1/10W-1%,R2 R3,100OHM-0603-1/10W-1%,0603,2, ,
7,,200OHM-0603-1/10W-1%,R1,200OHM-0603-1/10W-1%,0603,1, ,
8,,LOGO-LPLP,U$1,LOGO-LPLP,LOGO-LILYPAD,1, ,
9,,SEWTAP-NOHOLE2,U$2 U$3,SEWTAP-NOHOLE2,PETAL-NOHOLE-2SIDE,2, ,
10,,SEWTAP6,U$7 U$8 U$9 U$10,SEWTAP6,PETAL-SMALL-2SIDE,4, ,





Project info:
Schematic:,working
Variant:,default
Revision:,
Date:,2023-08-06_12-56-04
KiCad Version:,7.0.6-7.0.6~ubuntu22.04.1
Statistics:
Component Groups:,10
Component Count:,15 (0 SMD/ 0 THT)
Fitted Components:,15 (0 SMD/ 0 THT)
Number of PCBs:,1
Total Components:,15

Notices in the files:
projects/sparkfun_lilypad_reed_switch/version_current/working/working.kicad_sch:
Released under the Creative Commons
projects/sparkfun_lilypad_simplesnap_protoboard/version_current/working/working.kicad_sch:
Released under the Creative Commons Attribution Share-Alike 3.0 License
http://creativecommons.org/licenses/by-sa/3.0
parts and their libraries:
Released under the Creative Commons Attribution Share-Alike 4.0 License
